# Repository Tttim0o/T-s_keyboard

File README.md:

# T-s_keyboard
I always wanted to try and build a keyboard, then I found hackclub Keeb, a YouShip-WeShip program whitch guides you through the full process of designing the keyboard and even pays the whole keyboard for you.
This keyboard is mixture of no knowlage about pcbs, keyboards... It has 15 collums and 5 rows of keys in the 75 % layout, it has 3 macro keys a display and a rotary encoder. During the proces of building my 
own keyboard a learned a lot (pcb design, cad design..) and it was  really fun. the whole process lasted about 15 hours. 
The full assembly can be found here : https://cad.onshape.com/documents/07525d2c89944d0c9db79883/w/3a9a80255af722705f642198/e/c1f462bced7617f7b121b219?renderMode=0&uiState=6ae5cb62105f184d79b0cf5c
here are some photos from the prcoess:
keyboard completed:

making the screw holes in the case:

working on the case:

importing the pcb

pcb complete:

designing the pcb

Also sorry for the low quality of some photos.

AI Disclosure:
During this project i used ai for better understanding and learning of CAD, for finding major, minor flaws in the pcb.....

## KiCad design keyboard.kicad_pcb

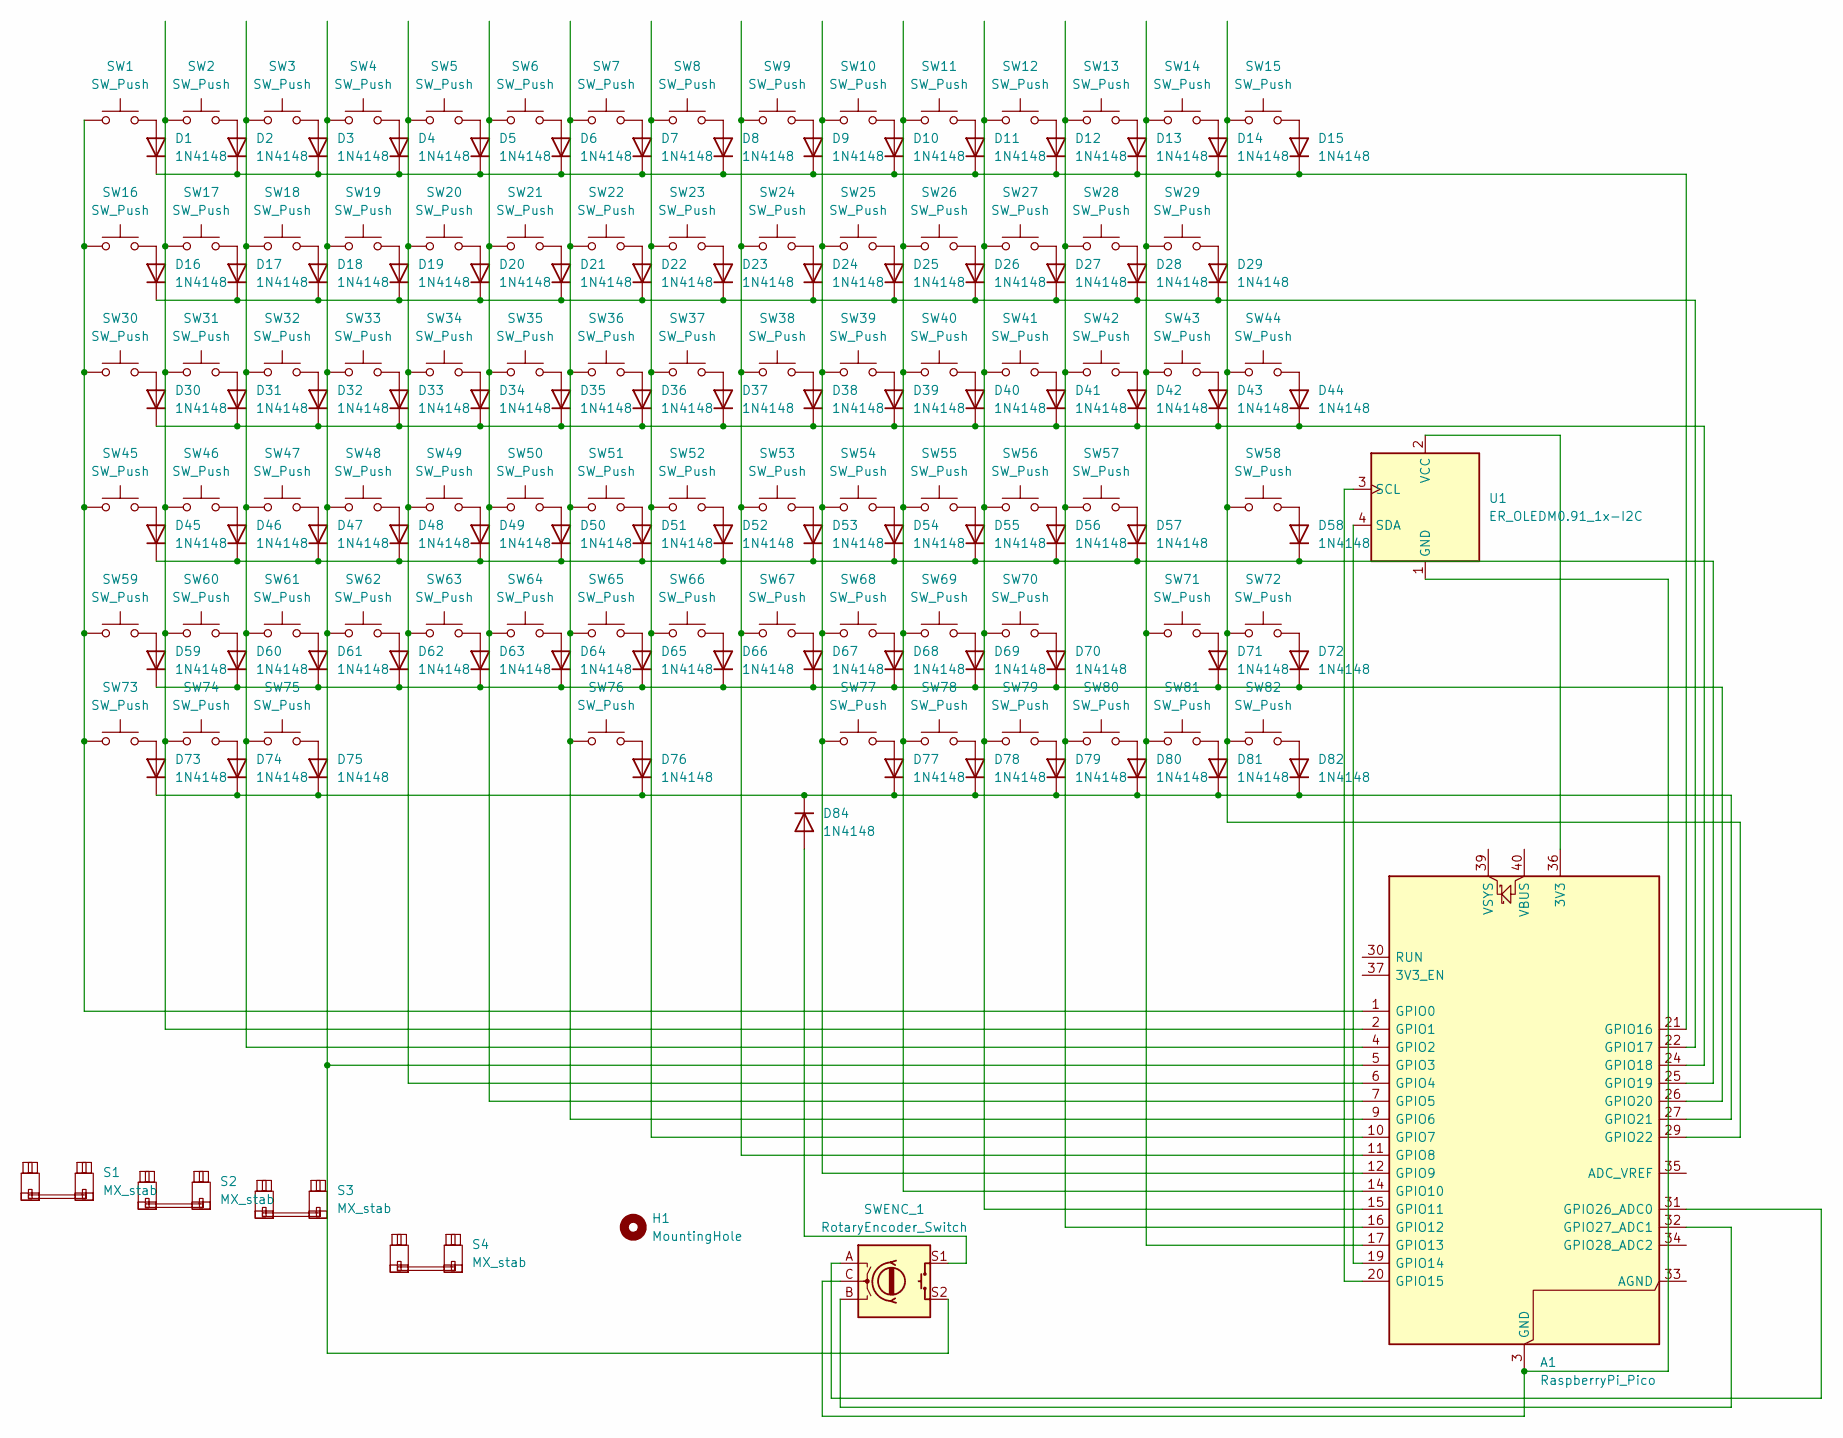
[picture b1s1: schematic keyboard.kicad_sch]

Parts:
A1: RaspberryPi_Pico; RaspberryPi_Pico_Common_Unspecified
D1, D2, D3, D4, D5, D6, D7, D8, D9, D10, D11, D12, D13, D14, D15, D16, D17, D18, D19, D20, D21, D22, D23, D24, D25, D26, D27, D28, D29, D30, D31, D32, D33, D34, D35, D36, D37, D38, D39, D40, D41, D42, D43, D44, D45, D46, D47, D48, D49, D50, D51, D52, D53, D54, D55, D56, D57, D58, D59, D60, D61, D62, D63, D64, D65, D66, D67, D68, D69, D70, D71, D72, D73, D74, D75, D76, D77, D78, D79, D80, D81, D82, D84: 1N4148; D_DO-35_SOD27_P7.62mm_Horizontal
H1: MountingHole; MountingHole_2.1mm
S1, S3, S4: MX_stab; Alps-MX-Stabilizers-2U
S2: MX_stab; STAB_MX_6u
SW1, SW2, SW3, SW4, SW5, SW6, SW7, SW8, SW9, SW10, SW11, SW12, SW13, SW14, SW15, SW16, SW17, SW18, SW19, SW20, SW21, SW22, SW23, SW24, SW25, SW26, SW27, SW28, SW29, SW30, SW31, SW32, SW33, SW34, SW35, SW36, SW37, SW38, SW39, SW40, SW41, SW42, SW43, SW44, SW45, SW46, SW47, SW48, SW49, SW50, SW51, SW52, SW53, SW54, SW55, SW56, SW57, SW58, SW59, SW60, SW61, SW62, SW63, SW64, SW65, SW66, SW67, SW68, SW69, SW70, SW71, SW72, SW73, SW74, SW75, SW76, SW77, SW78, SW79, SW80, SW81, SW82: SW_Push; SW_MX_3d_keycap_1u
SWENC_1: RotaryEncoder_Switch; RotaryEncoder_Alps_EC11E-Switch_Vertical_H20mm
U1: ER_OLEDM0.91_1x-I2C; SSD1306_0.96_Oled

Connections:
unnamed: A1.36 (3V3), U1.2 (VCC)
unnamed: A1.1 (GPIO0), SW1.1, SW16.1, SW30.1, SW45.1, SW59.1, SW73.1
unnamed: A1.2 (GPIO1), SW2.1, SW17.1, SW31.1, SW46.1, SW60.1, SW74.1
unnamed: A1.4 (GPIO2), SW3.1, SW18.1, SW32.1, SW47.1, SW61.1, SW75.1
unnamed: A1.5 (GPIO3), SW4.1, SW19.1, SW33.1, SW48.1, SW62.1, SWENC_1.S2
unnamed: A1.6 (GPIO4), SW5.1, SW20.1, SW34.1, SW49.1, SW63.1
unnamed: A1.7 (GPIO5), SW6.1, SW21.1, SW35.1, SW50.1, SW64.1
unnamed: A1.9 (GPIO6), SW7.1, SW22.1, SW36.1, SW51.1, SW65.1, SW76.1
unnamed: A1.10 (GPIO7), SW8.1, SW23.1, SW37.1, SW52.1, SW66.1
unnamed: A1.11 (GPIO8), SW9.1, SW24.1, SW38.1, SW53.1, SW67.1
unnamed: A1.12 (GPIO9), SW10.1, SW25.1, SW39.1, SW54.1, SW68.1, SW77.1
unnamed: A1.14 (GPIO10), SW11.1, SW26.1, SW40.1, SW55.1, SW69.1, SW78.1
unnamed: A1.15 (GPIO11), SW12.1, SW27.1, SW41.1, SW56.1, SW70.1, SW79.1
unnamed: A1.16 (GPIO12), SW13.1, SW28.1, SW42.1, SW57.1, SW80.1
unnamed: A1.17 (GPIO13), SW14.1, SW29.1, SW43.1, SW71.1, SW81.1
unnamed: A1.19 (GPIO14), U1.4 (SDA)
unnamed: A1.20 (GPIO15), U1.3 (SCL)
unnamed: A1.21 (GPIO16), D1.1 (K), D2.1 (K), D3.1 (K), D4.1 (K), D5.1 (K), D6.1 (K), D7.1 (K), D8.1 (K), D9.1 (K), D10.1 (K), D11.1 (K), D12.1 (K), D13.1 (K), D14.1 (K), D15.1 (K)
unnamed: A1.22 (GPIO17), D16.1 (K), D17.1 (K), D18.1 (K), D19.1 (K), D20.1 (K), D21.1 (K), D22.1 (K), D23.1 (K), D24.1 (K), D25.1 (K), D26.1 (K), D27.1 (K), D28.1 (K), D29.1 (K)
unnamed: A1.24 (GPIO18), D30.1 (K), D31.1 (K), D32.1 (K), D33.1 (K), D34.1 (K), D35.1 (K), D36.1 (K), D37.1 (K), D38.1 (K), D39.1 (K), D40.1 (K), D41.1 (K), D42.1 (K), D43.1 (K), D44.1 (K)
unnamed: A1.25 (GPIO19), D45.1 (K), D46.1 (K), D47.1 (K), D48.1 (K), D49.1 (K), D50.1 (K), D51.1 (K), D52.1 (K), D53.1 (K), D54.1 (K), D55.1 (K), D56.1 (K), D57.1 (K), D58.1 (K)
unnamed: A1.26 (GPIO20), D59.1 (K), D60.1 (K), D61.1 (K), D62.1 (K), D63.1 (K), D64.1 (K), D65.1 (K), D66.1 (K), D67.1 (K), D68.1 (K), D69.1 (K), D70.1 (K), D71.1 (K), D72.1 (K)
unnamed: A1.27 (GPIO21), D73.1 (K), D74.1 (K), D75.1 (K), D76.1 (K), D77.1 (K), D78.1 (K), D79.1 (K), D80.1 (K), D81.1 (K), D82.1 (K), D84.1 (K)
unnamed: A1.29 (GPIO22), SW15.1, SW44.1, SW58.1, SW72.1, SW82.1
unnamed: A1.31 (GPIO26_ADC0), SWENC_1.A
unnamed: A1.32 (GPIO27_ADC1), SWENC_1.B
unnamed: D1.2 (A), SW1.2
unnamed: D2.2 (A), SW2.2
unnamed: D3.2 (A), SW3.2
unnamed: D4.2 (A), SW4.2
unnamed: D5.2 (A), SW5.2
unnamed: D6.2 (A), SW6.2
unnamed: D7.2 (A), SW7.2
unnamed: D8.2 (A), SW8.2
unnamed: D9.2 (A), SW9.2
unnamed: D10.2 (A), SW10.2
unnamed: D11.2 (A), SW11.2
unnamed: D12.2 (A), SW12.2
unnamed: D13.2 (A), SW13.2
unnamed: D14.2 (A), SW14.2
unnamed: D15.2 (A), SW15.2
unnamed: D16.2 (A), SW16.2
unnamed: D17.2 (A), SW17.2
unnamed: D18.2 (A), SW18.2
unnamed: D19.2 (A), SW19.2
unnamed: D20.2 (A), SW20.2
unnamed: D21.2 (A), SW21.2
unnamed: D22.2 (A), SW22.2
unnamed: D23.2 (A), SW23.2
unnamed: D24.2 (A), SW24.2
unnamed: D25.2 (A), SW25.2
unnamed: D26.2 (A), SW26.2
unnamed: D27.2 (A), SW27.2
unnamed: D28.2 (A), SW28.2
unnamed: D29.2 (A), SW29.2
unnamed: D30.2 (A), SW30.2
unnamed: D31.2 (A), SW31.2
unnamed: D32.2 (A), SW32.2
unnamed: D33.2 (A), SW33.2
unnamed: D34.2 (A), SW34.2
unnamed: D35.2 (A), SW35.2
unnamed: D36.2 (A), SW36.2
unnamed: D37.2 (A), SW37.2
unnamed: D38.2 (A), SW38.2
unnamed: D39.2 (A), SW39.2
unnamed: D40.2 (A), SW40.2
unnamed: D41.2 (A), SW41.2
unnamed: D42.2 (A), SW42.2
unnamed: D43.2 (A), SW43.2
unnamed: D44.2 (A), SW44.2
unnamed: D45.2 (A), SW45.2
unnamed: D46.2 (A), SW46.2
unnamed: D47.2 (A), SW47.2
unnamed: D48.2 (A), SW48.2
unnamed: D49.2 (A), SW49.2
unnamed: D50.2 (A), SW50.2
unnamed: D51.2 (A), SW51.2
unnamed: D52.2 (A), SW52.2
unnamed: D53.2 (A), SW53.2
unnamed: D54.2 (A), SW54.2
unnamed: D55.2 (A), SW55.2
unnamed: D56.2 (A), SW56.2
unnamed: D57.2 (A), SW57.2
unnamed: D58.2 (A), SW58.2
unnamed: D59.2 (A), SW59.2
unnamed: D60.2 (A), SW60.2
unnamed: D61.2 (A), SW61.2
unnamed: D62.2 (A), SW62.2
unnamed: D63.2 (A), SW63.2
unnamed: D64.2 (A), SW64.2
unnamed: D65.2 (A), SW65.2
unnamed: D66.2 (A), SW66.2
unnamed: D67.2 (A), SW67.2
unnamed: D68.2 (A), SW68.2
unnamed: D69.2 (A), SW69.2
unnamed: D70.2 (A), SW70.2
unnamed: D71.2 (A), SW71.2
unnamed: D72.2 (A), SW72.2
unnamed: D73.2 (A), SW73.2
unnamed: D74.2 (A), SW74.2
unnamed: D75.2 (A), SW75.2
unnamed: D76.2 (A), SW76.2
unnamed: D77.2 (A), SW77.2
unnamed: D78.2 (A), SW78.2
unnamed: D79.2 (A), SW79.2
unnamed: D80.2 (A), SW80.2
unnamed: D81.2 (A), SW81.2
unnamed: D82.2 (A), SW82.2
unnamed: D84.2 (A), SWENC_1.S1
unnamed: A1.3 (GND), A1.8 (GND), A1.13 (GND), A1.18 (GND), A1.23 (GND), A1.28 (GND), A1.38 (GND), SWENC_1.C, U1.1 (GND)

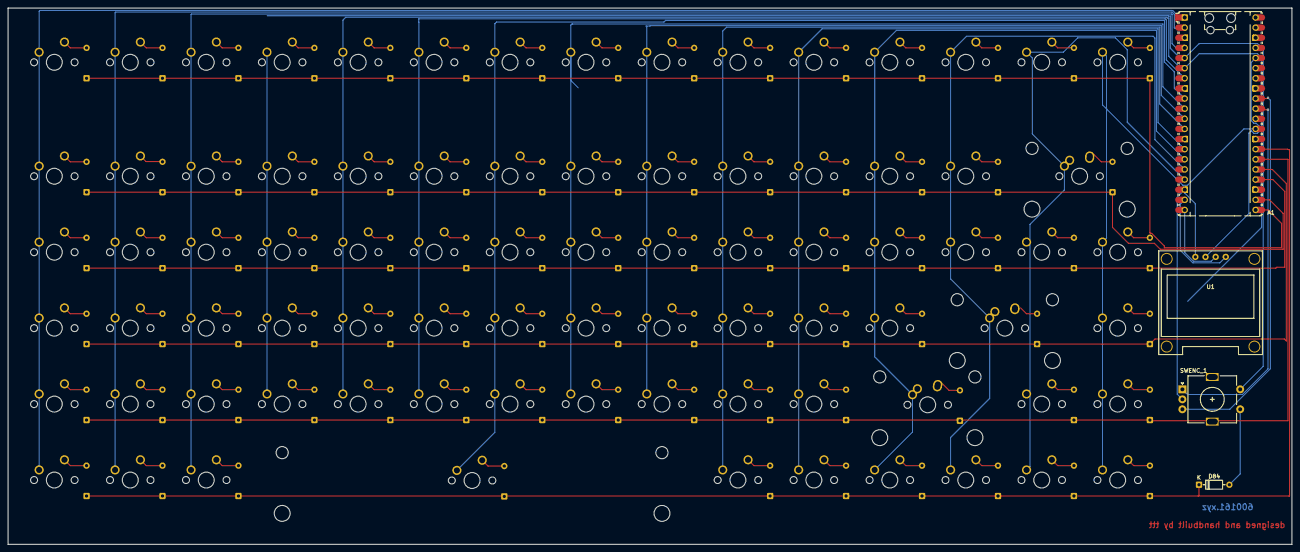
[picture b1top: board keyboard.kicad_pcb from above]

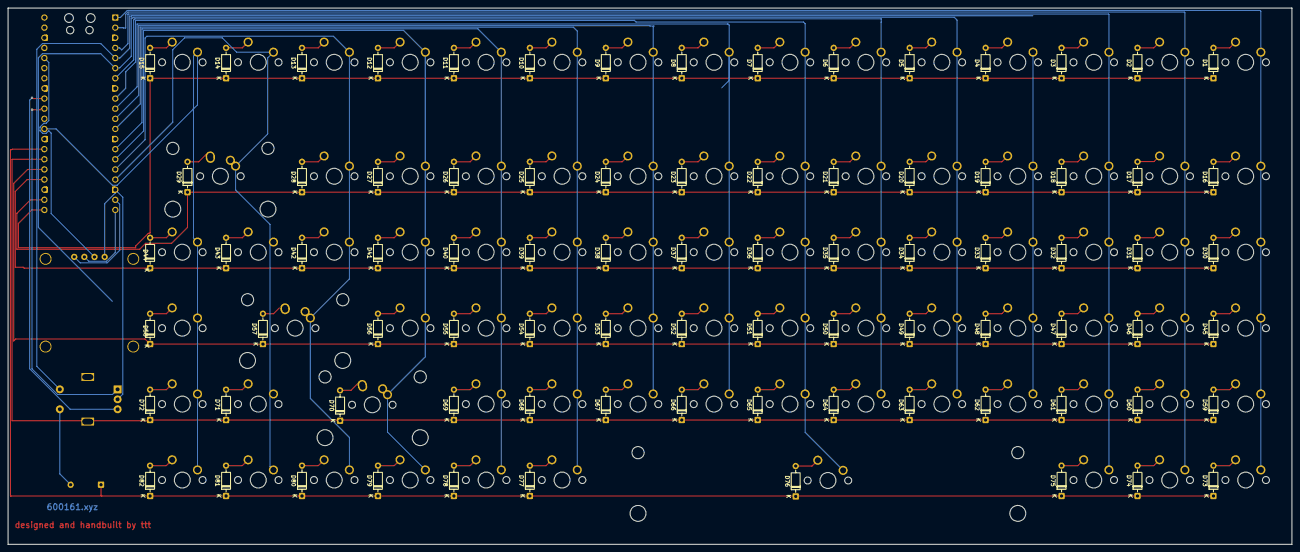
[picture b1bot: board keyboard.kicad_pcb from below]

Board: 2 copper layers, 322.0 x 134.5 mm, 173 parts (82 on the bottom side), 110 nets.
